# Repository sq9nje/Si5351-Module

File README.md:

Si5351-Module
=============

EAGLE files for a simple Si5351A breakout board. The module has Si5351A in a MSOP package, a level translator for the I2C bus and a 3.3V vaoltage regulator. 3 outputs with end-launch SMA connectors.

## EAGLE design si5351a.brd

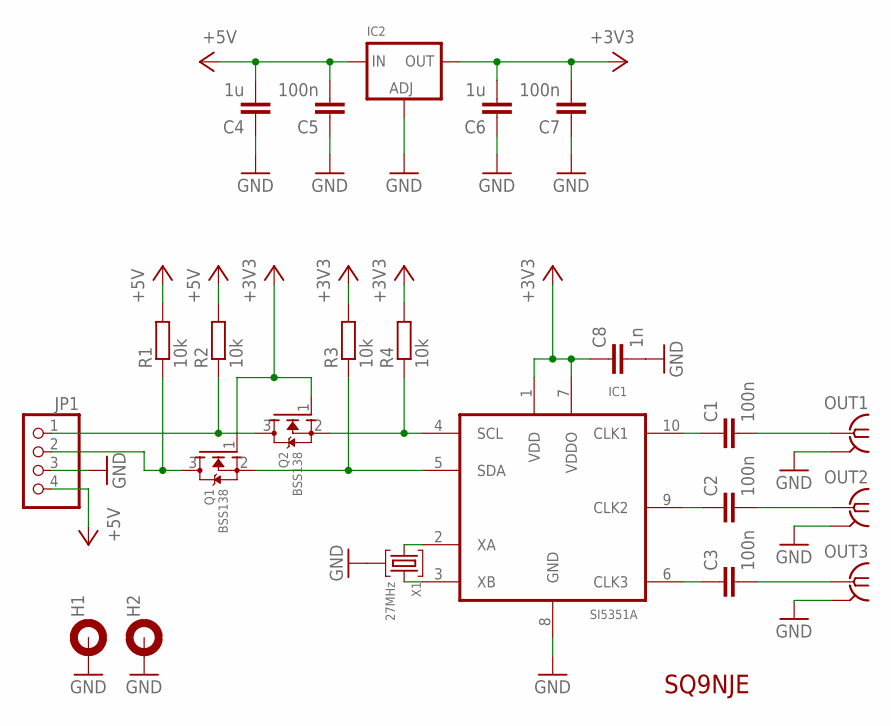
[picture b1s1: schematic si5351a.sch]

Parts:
C1, C2, C3, C5, C7: 100n; 0805
C4, C6: 1u; 0805
C8: 1n; 0805
H1, H2: MOUNT-PAD-ROUND3.0; 3,0-PAD
IC1: SI5351A; MSOP10
IC2: LM1117SOT223-REFLOW; SOT223-R
JP1: PINHD-1X04_2.54-90°; 1X04/90
OUT1, OUT2, OUT3: SMA-142-0711-821/826; J502-ND-142-0711-821/826
Q1, Q2: BSS138; SOT23-R
R1, R2, R3, R4: 10k; 0805
U$1: SQ9NJE
X1: 27MHz; TXC

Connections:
+3V3: C6.2, C7.2, C8.1, IC1.1 (VDD), IC1.7 (VDDO), IC2.2 (OUT), Q1.1 (G), Q2.1 (G), R3.2, R4.2
+5V: C4.2, C5.2, IC2.3 (IN), JP1.4, R1.2, R2.2
GND: C4.1, C5.1, C6.1, C7.1, C8.2, H1.B3,0, H2.B3,0, IC1.8 (GND), IC2.1 (ADJ), JP1.3, OUT1.G@1 (2), OUT1.G@2 (2), OUT1.G@3 (2), OUT1.G@4 (2), OUT2.G@1 (2), OUT2.G@2 (2), OUT2.G@3 (2), OUT2.G@4 (2), OUT3.G@1 (2), OUT3.G@2 (2), OUT3.G@3 (2), OUT3.G@4 (2), X1.2, X1.4 (2)
unnamed: IC1.2 (XA), X1.1
unnamed: IC1.3 (XB), X1.3
unnamed: IC1.4 (SCL), Q2.2 (S), R4.1
unnamed: IC1.5 (SDA), Q1.2 (S), R3.1
unnamed: C1.1, IC1.10 (CLK1)
unnamed: JP1.1, Q2.3 (D), R2.1
unnamed: JP1.2, Q1.3 (D), R1.1
unnamed: C2.1, IC1.9 (CLK2)
unnamed: C3.1, IC1.6 (CLK3)
unnamed: C3.2, OUT3.1
unnamed: C1.2, OUT1.1
unnamed: C2.2, OUT2.1

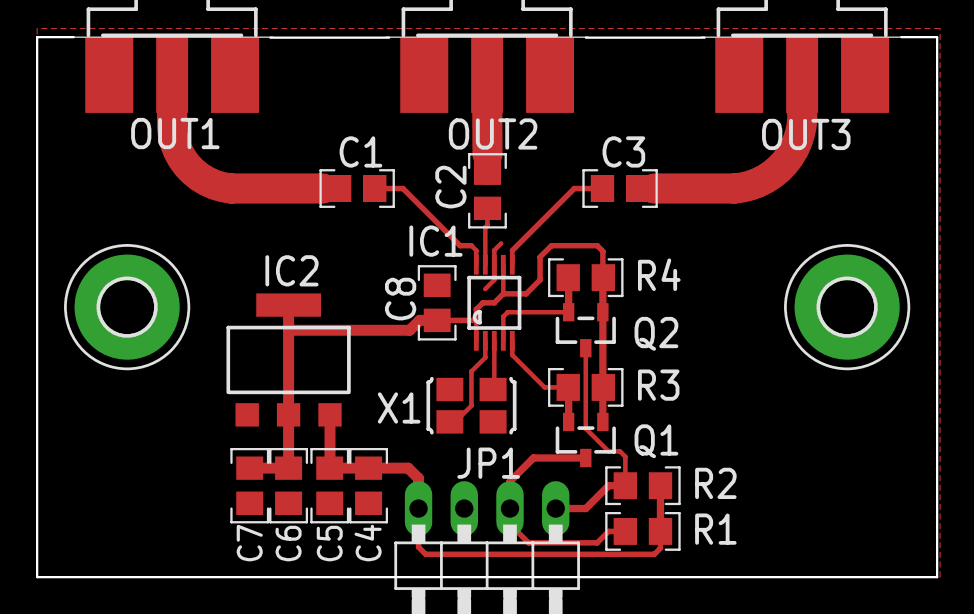
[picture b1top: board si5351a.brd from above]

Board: 2 copper layers, 50.0 x 30.0 mm, 24 parts (0 on the bottom side), 15 nets.

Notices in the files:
parts and their libraries:
microbuilder: This work is placed in the public domain, and may be freely used for commercial and non-commercial work with the following conditions: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
